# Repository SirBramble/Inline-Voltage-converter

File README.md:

# The Vuwu inline voltage converter

This Project is a small adjustable Buck-Boost converter board, designed to be fitted inline with a Power Cable. It's only 14mmx22mm making it ideal for splicing in to a cable and wrapping it with heat shrink. The connectors used are *2 pin JST PH 2.0 SMD vertical*. A Link to them can be found [here](https://de.aliexpress.com/item/1005004938361514.html?spm=a2g0o.order_list.order_list_main.4.70475c5fH9vSV2&gatewayAdapt=glo2deu).

## Ordering

The design files for KiCad are located in the folders. Alternatively you can use the GERBER Files with a preconfigured BOM to order them from JLCPCB.

## Setting the Voltage

Due to the small size of the board, adding a potentiometer was not possible.
The output voltage can be set via the $R_4$ Resistor located on the back of the PCB. $R_4$ is calculated as follows:

$$R_4 = R_3 \cdot \left(\frac{V_{OUT}}{V_{REF}} - 1\right) = 10k\Omega \cdot \left(\frac{V_{OUT}}{0.8V} - 1\right)$$

Alternatively there is a small conversion table for common voltages:

|$V_{OUT}$|    $R_4$   |
| ------- | ---------- |
|  $3V3$  | $31k\Omega$|
|  $5V$   | $53k\Omega$|
|  $5V3$  | $56k\Omega$|
|  $5V5$  | $59k\Omega$|

**Important:** The [TPS63070](https://www.ti.com/lit/ds/symlink/tps63070.pdf?ts=1701570165058&ref_url=https%253A%252F%252Fwww.ti.com%252Fproduct%252Fde-de%252FTPS63070) only has a output Voltage Rage of $2.5V$ to $9V$ and an approximate max. current of $2A$. For more information, see the [datasheet](https://www.ti.com/lit/ds/symlink/tps63070.pdf?ts=1701570165058&ref_url=https%253A%252F%252Fwww.ti.com%252Fproduct%252Fde-de%252FTPS63070).

## Pictures

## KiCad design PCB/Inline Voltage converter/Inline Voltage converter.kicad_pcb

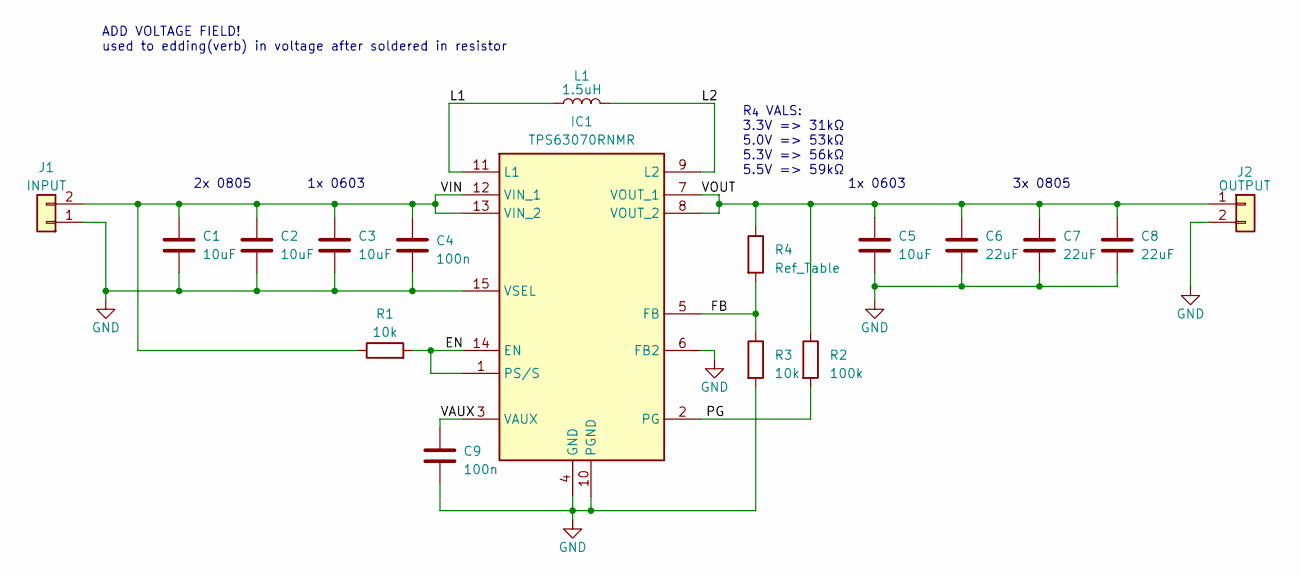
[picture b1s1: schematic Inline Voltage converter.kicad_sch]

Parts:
C1, C2: 10uF; C_0805_2012Metric; LCSC C440198
C3, C5: 10uF; C_0603_1608Metric; LCSC C96446
C4, C9: 100n; C_0603_1608Metric; LCSC C14663
C6, C7, C8: 22uF; C_0805_2012Metric; LCSC C45783
IC1: TPS63070RNMR; TPS630701RNMR; Mouser Part Number 595-TPS63070RNMR
J1: INPUT; JST_PH_S2B-PH-SM4-TB_1x02-1MP_P2.00mm_Horizontal
J2: OUTPUT; JST_PH_S2B-PH-SM4-TB_1x02-1MP_P2.00mm_Horizontal
L1: 1.5uH; L_Chilisin_BMRA00050530; LCSC C436532
R1, R3: 10k; R_0603_1608Metric; LCSC C25804
R2: 100k; R_0603_1608Metric; LCSC C25803
R4: Ref_Table; R_0603_1608Metric

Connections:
/EN: IC1.1 (PS/S), IC1.14 (EN), R1.2
/FB: IC1.5 (FB), R3.1, R4.2
/L1: IC1.11 (L1), L1.1
/L2: IC1.9 (L2), L1.2
/PG: IC1.2 (PG), R2.2
/VAUX: C9.1, IC1.3 (VAUX)
/VIN: C1.1, C2.1, C3.1, C4.1, IC1.12 (VIN_1), IC1.13 (VIN_2), J1.2, R1.1
/VOUT: C5.1, C6.1, C7.1, C8.1, IC1.7 (VOUT_1), IC1.8 (VOUT_2), J2.1, R2.1, R4.1
GND: C1.2, C2.2, C3.2, C4.2, C5.2, C6.2, C7.2, C8.2, C9.2, IC1.4 (GND), IC1.6 (FB2), IC1.10 (PGND), IC1.15 (VSEL), J1.1, J2.2, R3.2

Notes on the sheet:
2x 0805 1x 0603
R_{4} VALS: 3.3V => 31kΩ 5.0V => 53kΩ 5.3V => 56kΩ 5.5V => 59kΩ
1x 0603
ADD VOLTAGE FIELD! used to edding(verb) in voltage after soldered in resistor
3x 0805

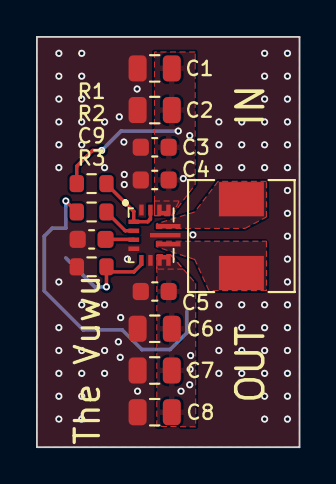
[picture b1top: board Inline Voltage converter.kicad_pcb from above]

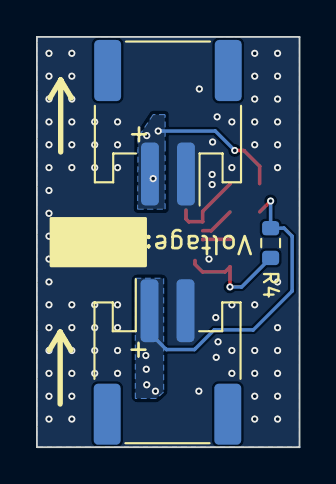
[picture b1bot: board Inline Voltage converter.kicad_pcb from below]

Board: 2 copper layers, 14.6 x 22.8 mm, 17 parts (3 on the bottom side), 9 nets.

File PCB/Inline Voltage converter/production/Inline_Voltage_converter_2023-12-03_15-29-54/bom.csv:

Designator,Footprint,Quantity,Value,LCSC Part #
"C1, C2",0805,2,10uF,C440198
"C3, C5",0603,2,10uF,C96446
"C4, C9",0603,2,100n,C14663
"C6, C7, C8",0805,3,22uF,C45783
IC1,TPS630701RNMR,1,TPS63070RNMR,C109322
L1,L_Chilisin_BMRA00050530,1,1.5uH,C436532
"R1, R3",0603,2,10k,C25804
R2,0603,1,100k,C25803

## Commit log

2023-12-03 added 3d mod
